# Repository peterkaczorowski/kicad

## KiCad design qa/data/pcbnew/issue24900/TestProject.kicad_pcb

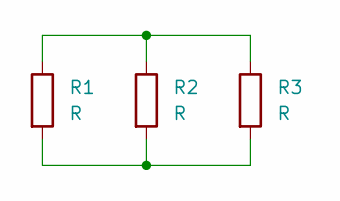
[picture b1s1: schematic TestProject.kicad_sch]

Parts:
R1, R2, R3: R; R_0603_1608Metric

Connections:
unnamed: R1.1, R2.1, R3.1
unnamed: R1.2, R2.2, R3.2

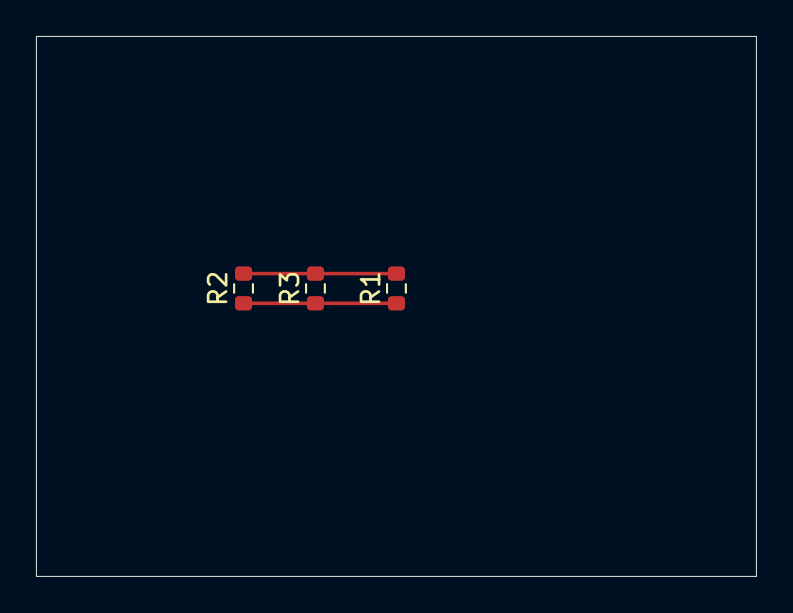
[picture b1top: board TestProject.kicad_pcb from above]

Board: 2 copper layers, 40.0 x 30.0 mm, 3 parts (0 on the bottom side), 2 nets.
